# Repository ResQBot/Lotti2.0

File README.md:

# Lotti2.0 by Res.Q Bots Austria

Lotti2.0 is the seccond generation of our tracked **U**rban **S**earch and **E**xploration **R**obot (or USER).

We hope that any info you find in this repository helps you in your quest to develop your own USER, or robot of any other kind.
If you have any questions or want to partner up, feel free to contact us.

## Repository content:

### getting_started
contains a (more or less) detailed introduction to the whole topic of using Ubuntu and ROS, using our ROS packages and how to develop your own. This is a work in progress and you will definitely need addittional information to get deeper into ROS development.

### hardware
contains all (more or less) the hardware information and the CAD files.

### resources
contains user manuals, guidebooks, datasheets, etc. for motory, sensors, parts, ... used in our current robot.

### src 
contains our **ROS2 code** to control the robot and make use of its sensors.

### external

[#external](#external)

Enthält externe Abhängigkeiten, die als Git-Submodule eingebunden sind:

- **[athena](https://github.com/tu-darmstadt-ros-pkg/athena)** (TU Darmstadt) – wir nutzen daraus
  das ESP32-basierte E-Stop-System (`E-Stop`-Ordner im Submodule) für die Not-Aus-Funktionalität.
- **[hector_ros2_utils](https://github.com/tu-darmstadt-ros-pkg/hector_ros2_utils)** (TU Darmstadt) –
  Basis-Utility-Bibliothek, die von der E-Stop-ROS2-Node benötigt wird.

Beide Repos stehen unter MIT-Lizenz. Vielen Dank an das TU-Darmstadt-Team für die Bereitstellung!

#### Setup

Da dieses Repo Submodule enthält, beim Klonen unbedingt `--recurse-submodules` verwenden:

\`\`\`bash
git clone --recurse-submodules https://github.com/ResQBot/Lotti2.0.git
\`\`\`

Falls bereits ohne diese Option geklont wurde, nachträglich:

\`\`\`bash
git submodule update --init --recursive
\`\`\`
&nbsp;
## Disclaimer
Please remember, that we are not professionals in the field of robotics, but merely curious students fooling around. While (most) code and designs you'll find here may work for us, they might not work for you and we do not take any responsibility for potential danger arising from the use of our ideas.

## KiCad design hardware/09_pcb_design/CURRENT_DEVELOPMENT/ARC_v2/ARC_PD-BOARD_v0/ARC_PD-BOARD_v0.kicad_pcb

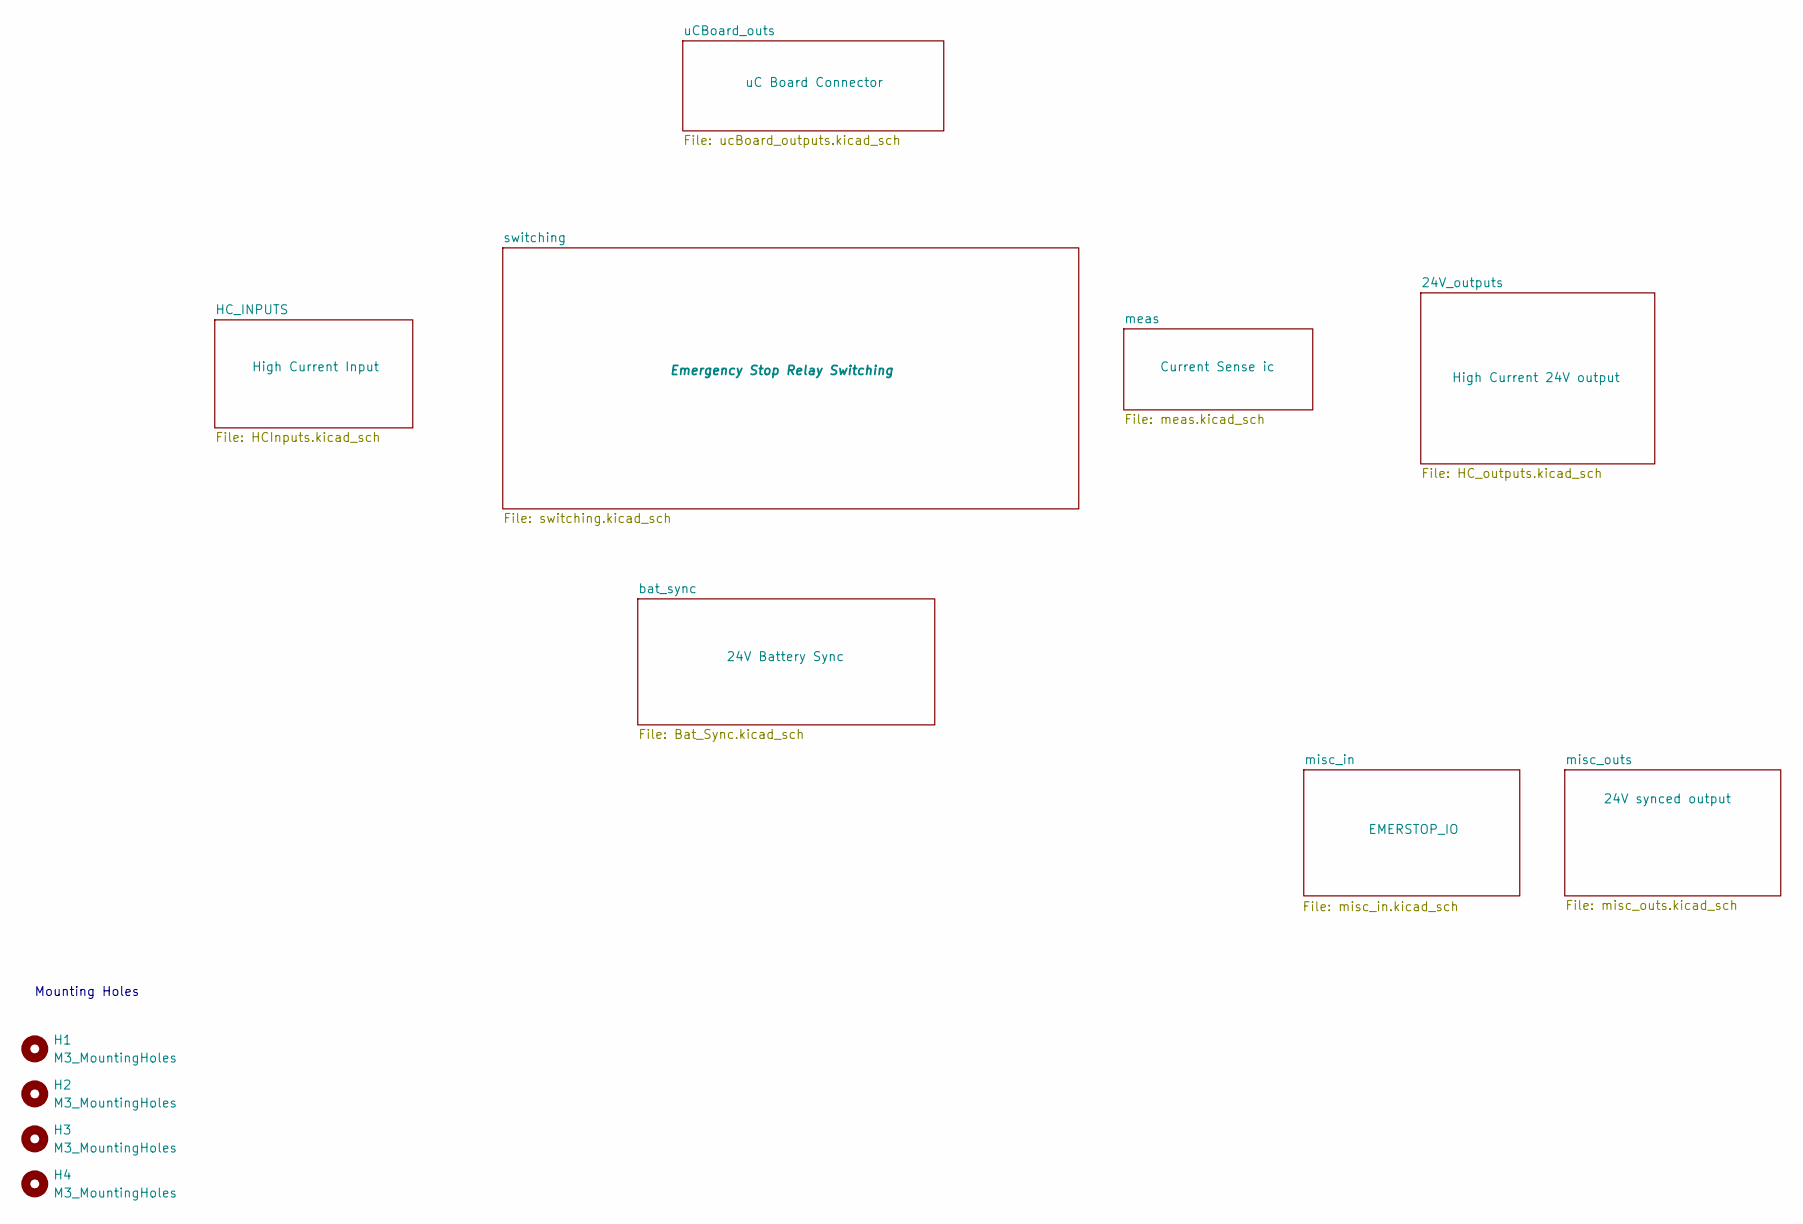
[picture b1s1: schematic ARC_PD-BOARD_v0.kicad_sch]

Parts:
H1, H2, H3, H4: M3_MountingHoles; MountingHole_3.2mm_M3

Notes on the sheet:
Mounting Holes

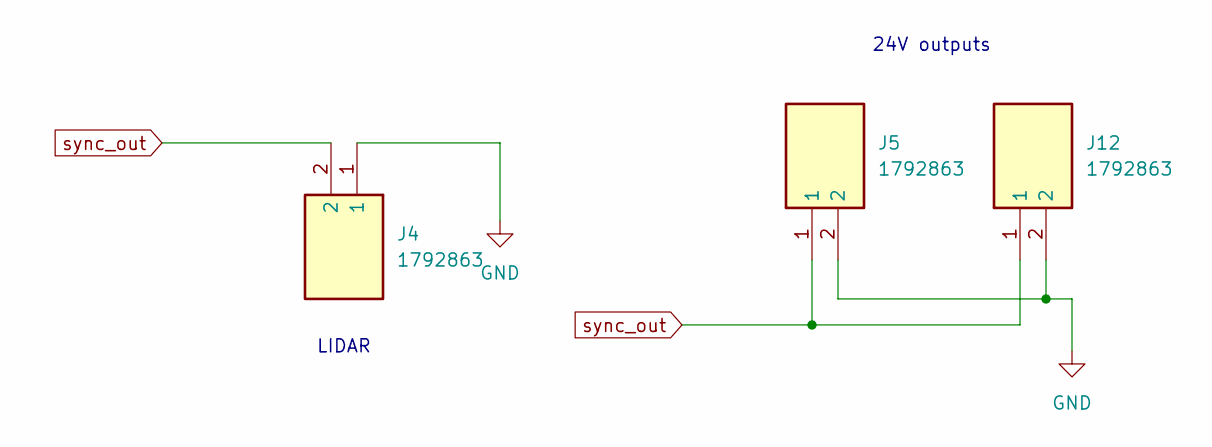
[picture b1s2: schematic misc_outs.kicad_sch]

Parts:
J4, J5, J12: 1792863; Mouser Part Number 651-1792863

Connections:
GND: J4.1, J5.2, J12.2; also elsewhere on the board
sync_out: J4.2, J5.1, J12.1; also elsewhere on the board

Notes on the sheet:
LIDAR
24V outputs

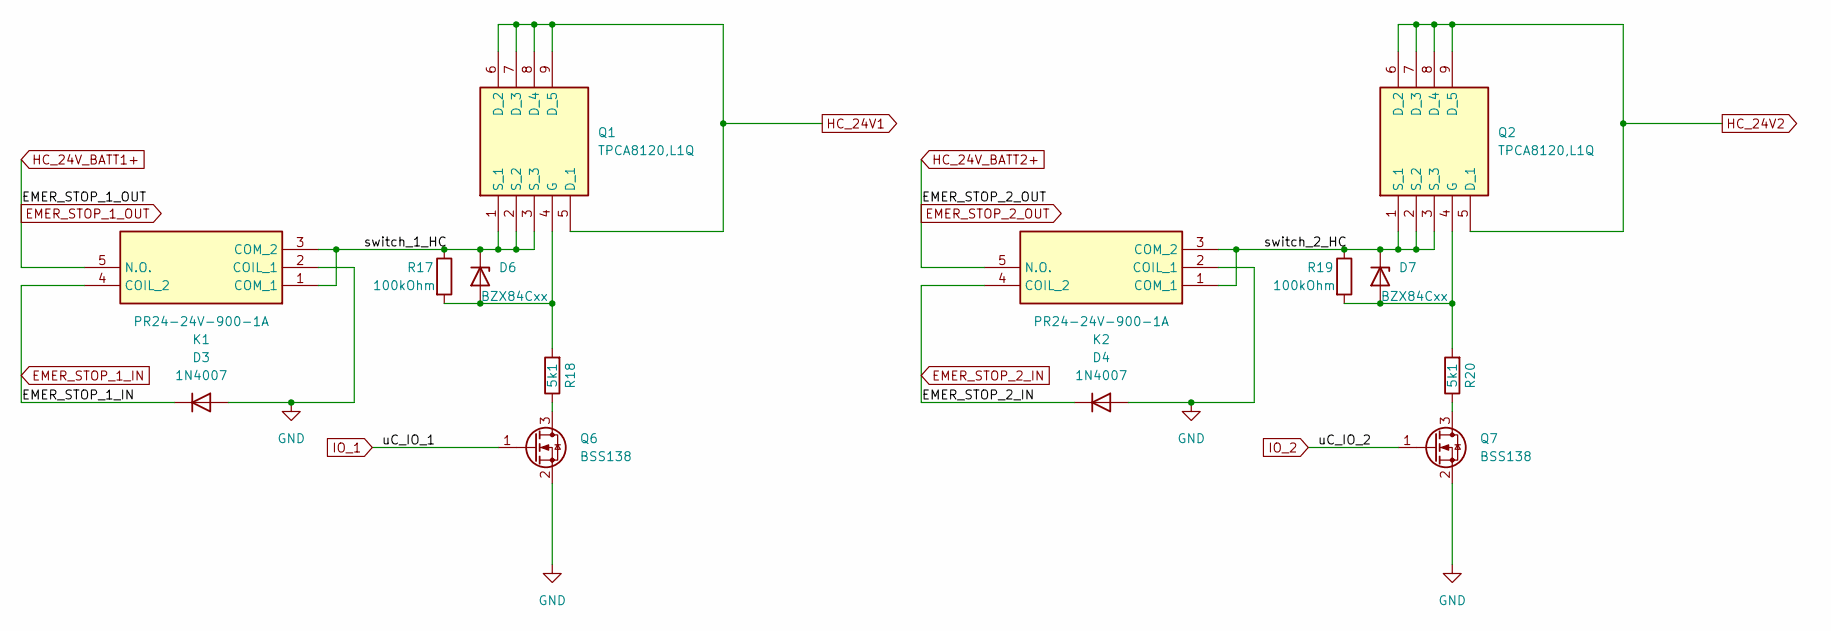
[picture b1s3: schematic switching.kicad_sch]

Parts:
D3, D4: 1N4007; D_DO-41_SOD81_P10.16mm_Horizontal
D6, D7: BZX84Cxx; SOT-23
K1, K2: PR24-24V-900-1A; PR2424V9001A; Mouser Part Number 179-PR24-24V-900-1A
Q1, Q2: TPCA8120,L1Q; TPH4R003NLL1Q; Mouser Part Number 757-TPCA8120L1Q
Q6, Q7: BSS138; SOT-23
R17, R19: 100kOhm; R_1206_3216Metric_Pad1.30x1.75mm_HandSolder
R18, R20: 5k1; R_1206_3216Metric_Pad1.30x1.75mm_HandSolder

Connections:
/switching/switch_1_HC: D6.3 (K), K1.1 (COM_1), K1.3 (COM_2), Q1.1 (S_1), Q1.2 (S_2), Q1.3 (S_3), R17.1
/switching/switch_2_HC: D7.3 (K), K2.1 (COM_1), K2.3 (COM_2), Q2.1 (S_1), Q2.2 (S_2), Q2.3 (S_3), R19.1
EMER_STOP_1_IN: D3.1 (K), K1.4 (COIL_2); also elsewhere on the board
EMER_STOP_1_OUT: K1.5 (N.O.); also elsewhere on the board
EMER_STOP_2_IN: D4.1 (K), K2.4 (COIL_2); also elsewhere on the board
EMER_STOP_2_OUT: K2.5 (N.O.); also elsewhere on the board
GND: D3.2 (A), D4.2 (A), K1.2 (COIL_1), K2.2 (COIL_1), Q6.2 (S), Q7.2 (S); also elsewhere on the board
HC_24V1: Q1.5 (D_1), Q1.6 (D_2), Q1.7 (D_3), Q1.8 (D_4), Q1.9 (D_5); also elsewhere on the board
HC_24V2: Q2.5 (D_1), Q2.6 (D_2), Q2.7 (D_3), Q2.8 (D_4), Q2.9 (D_5); also elsewhere on the board
IO_1: Q6.1 (G); also elsewhere on the board
IO_2: Q7.1 (G); also elsewhere on the board
unnamed: D6.1 (A), Q1.4 (G), R17.2, R18.2
unnamed: D7.1 (A), Q2.4 (G), R19.2, R20.2
unnamed: Q6.3 (D), R18.1
unnamed: Q7.3 (D), R20.1

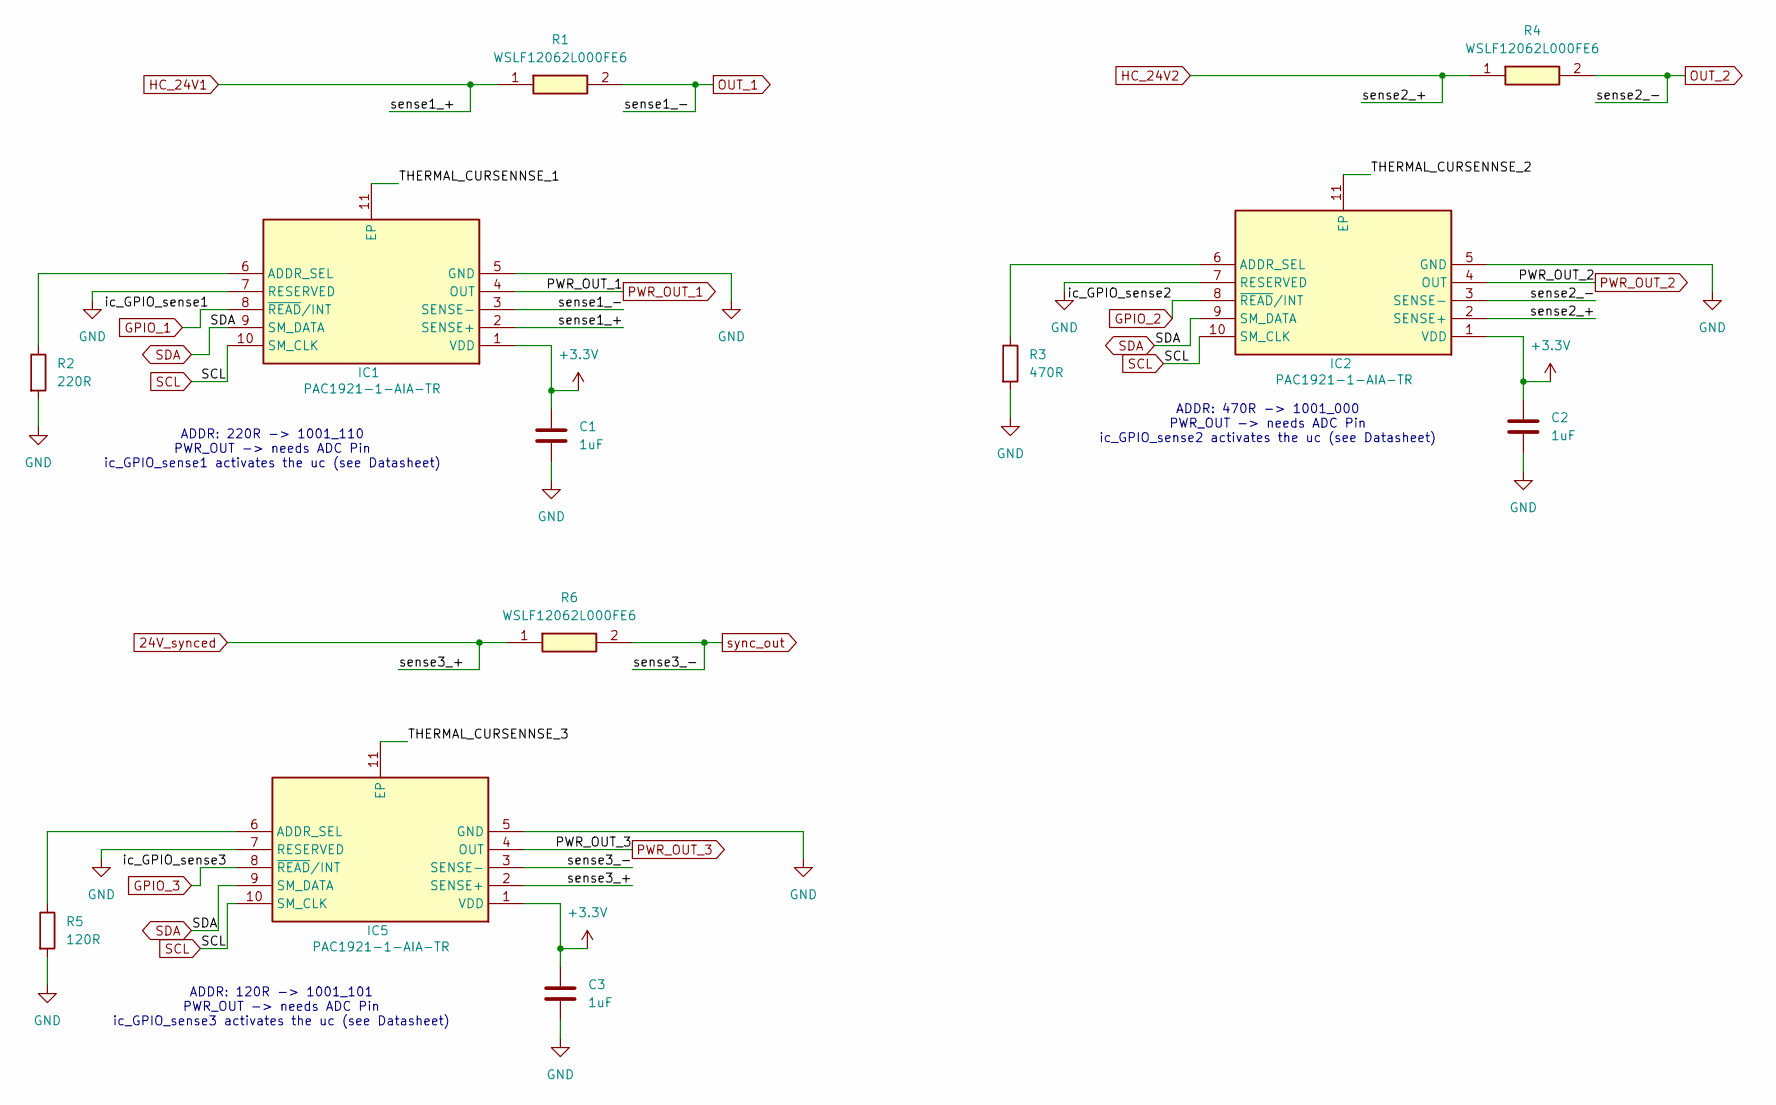
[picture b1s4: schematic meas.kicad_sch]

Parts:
C1, C2, C3: 1uF; C_1206_3216Metric_Pad1.33x1.80mm_HandSolder
IC1, IC2, IC5: PAC1921-1-AIA-TR; SON50P300X300X90-11N-D; Mouser Part Number 579-PAC1921-1-AIA-TR
R1, R4, R6: WSLF12062L000FE6; R_1206_3216Metric_Pad1.30x1.75mm_HandSolder; Manufacturer_Part_Number WSLF12062L000FE6
R2: 220R; R_0805_2012Metric_Pad1.20x1.40mm_HandSolder
R3: 470R; R_0805_2012Metric_Pad1.20x1.40mm_HandSolder
R5: 120R; R_0805_2012Metric_Pad1.20x1.40mm_HandSolder

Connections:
24V_synced: IC5.2 (SENSE+), R6.1; also elsewhere on the board
+3.3V: C1.1, C2.1, C3.1, IC1.1 (VDD), IC2.1 (VDD), IC5.1 (VDD); also elsewhere on the board
/meas/THERMAL_CURSENNSE_1: IC1.11 (EP)
/meas/THERMAL_CURSENNSE_2: IC2.11 (EP)
/meas/THERMAL_CURSENNSE_3: IC5.11 (EP)
GND: C1.2, C2.2, C3.2, IC1.5 (GND), IC1.7 (RESERVED), IC2.5 (GND), IC2.7 (RESERVED), IC5.5 (GND), IC5.7 (RESERVED), R2.2, R3.2, R5.2; also elsewhere on the board
GPIO_1: IC1.8 (~READ/INT); also elsewhere on the board
GPIO_2: IC2.8 (~READ/INT); also elsewhere on the board
GPIO_3: IC5.8 (~READ/INT); also elsewhere on the board
HC_24V1: IC1.2 (SENSE+), R1.1; also elsewhere on the board
HC_24V2: IC2.2 (SENSE+), R4.1; also elsewhere on the board
unnamed: IC1.6 (ADDR_SEL), R2.1
unnamed: IC2.6 (ADDR_SEL), R3.1
unnamed: IC5.6 (ADDR_SEL), R5.1
OUT_1: IC1.3 (SENSE-), R1.2; also elsewhere on the board
OUT_2: IC2.3 (SENSE-), R4.2; also elsewhere on the board
PWR_OUT_1: IC1.4 (OUT); also elsewhere on the board
PWR_OUT_2: IC2.4 (OUT); also elsewhere on the board
PWR_OUT_3: IC5.4 (OUT); also elsewhere on the board
SCL: IC1.10 (SM_CLK), IC2.10 (SM_CLK), IC5.10 (SM_CLK); also elsewhere on the board
SDA: IC1.9 (SM_DATA), IC2.9 (SM_DATA), IC5.9 (SM_DATA); also elsewhere on the board
sync_out: IC5.3 (SENSE-), R6.2; also elsewhere on the board

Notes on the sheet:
ADDR: 120R -> 1001_101 PWR_OUT -> needs ADC Pin ic_GPIO_sense3 activates the uc (see Datasheet)
ADDR: 220R -> 1001_110 PWR_OUT -> needs ADC Pin ic_GPIO_sense1 activates the uc (see Datasheet)
ADDR: 470R -> 1001_000 PWR_OUT -> needs ADC Pin ic_GPIO_sense2 activates the uc (see Datasheet)

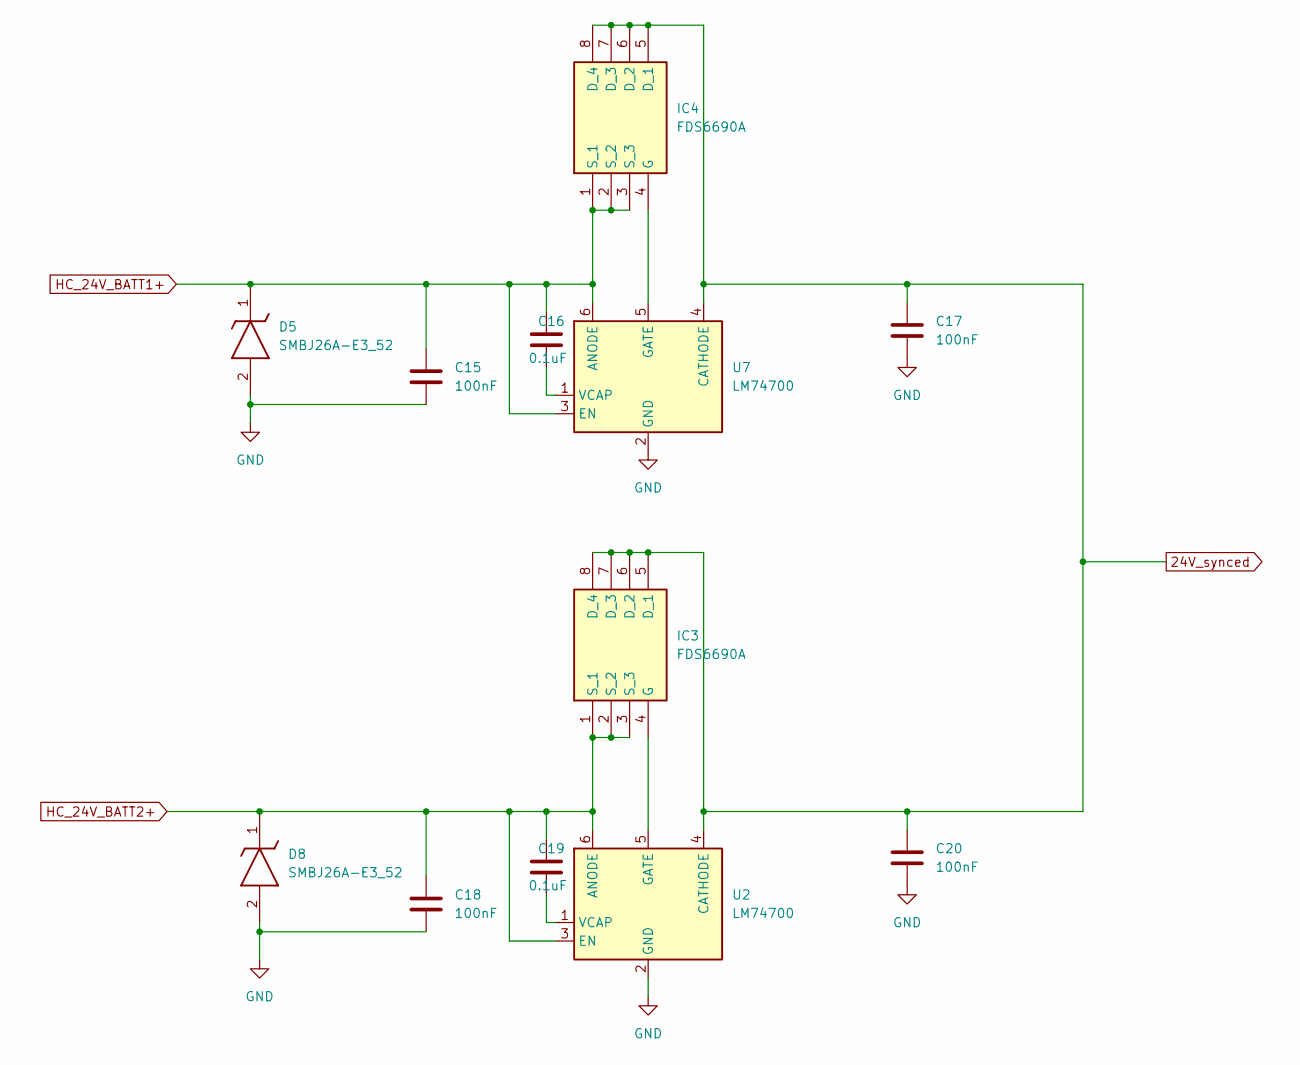
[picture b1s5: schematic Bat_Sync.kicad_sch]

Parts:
C15, C17, C18, C20: 100nF; C_0805_2012Metric_Pad1.18x1.45mm_HandSolder
C16, C19: 0.1uF; C_0805_2012Metric_Pad1.18x1.45mm_HandSolder
D5, D8: SMBJ26A-E3_52; DIOM5436X244N; Mouser Part Number 625-SMBJ26A-E3
IC3, IC4: FDS6690A; SOIC127P600X175-8N; Mouser Part Number 512-FDS6690A
U2, U7: LM74700; SOT-23-6

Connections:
24V_synced: C17.1, C20.1, IC3.5 (D_1), IC3.6 (D_2), IC3.7 (D_3), IC3.8 (D_4), IC4.5 (D_1), IC4.6 (D_2), IC4.7 (D_3), IC4.8 (D_4), U2.4 (CATHODE), U7.4 (CATHODE); also elsewhere on the board
EMER_STOP_1_OUT: C15.1, C16.1, D5.1 (K), IC4.1 (S_1), IC4.2 (S_2), IC4.3 (S_3), U7.3 (EN), U7.6 (ANODE); also elsewhere on the board
EMER_STOP_2_OUT: C18.1, C19.1, D8.1 (K), IC3.1 (S_1), IC3.2 (S_2), IC3.3 (S_3), U2.3 (EN), U2.6 (ANODE); also elsewhere on the board
GND: C15.2, C17.2, C18.2, C20.2, D5.2 (A), D8.2 (A), U2.2 (GND), U7.2 (GND); also elsewhere on the board
unnamed: IC3.4 (G), U2.5 (GATE)
unnamed: IC4.4 (G), U7.5 (GATE)
unnamed: C19.2, U2.1 (VCAP)
unnamed: C16.2, U7.1 (VCAP)

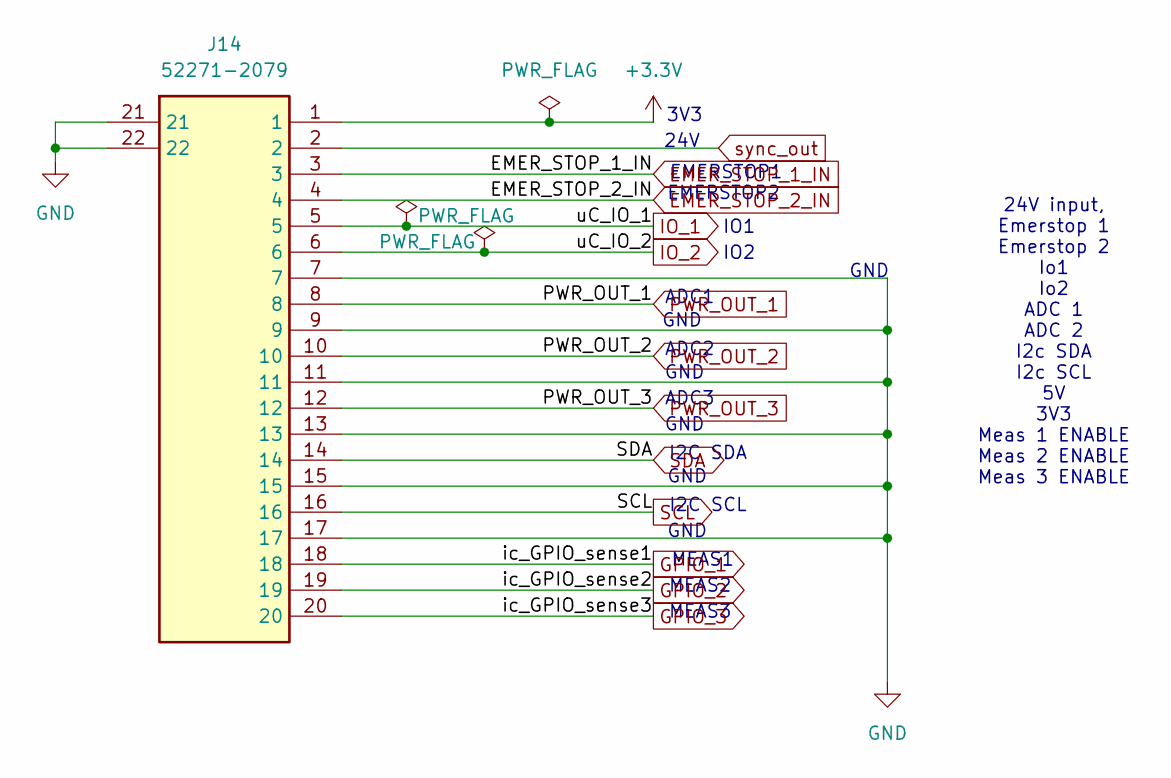
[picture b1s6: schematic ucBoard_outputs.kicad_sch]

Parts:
J14: 52271-2079; 522712079; Mouser Part Number 538-52271-2079

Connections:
+3.3V: J14.1; also elsewhere on the board
EMER_STOP_1_IN: J14.3; also elsewhere on the board
EMER_STOP_2_IN: J14.4; also elsewhere on the board
GND: J14.7, J14.9, J14.11, J14.13, J14.15, J14.17, J14.21, J14.22; also elsewhere on the board
GPIO_1: J14.18; also elsewhere on the board
GPIO_2: J14.19; also elsewhere on the board
GPIO_3: J14.20; also elsewhere on the board
IO_1: J14.5; also elsewhere on the board
IO_2: J14.6; also elsewhere on the board
PWR_OUT_1: J14.8; also elsewhere on the board
PWR_OUT_2: J14.10; also elsewhere on the board
PWR_OUT_3: J14.12; also elsewhere on the board
SCL: J14.16; also elsewhere on the board
SDA: J14.14; also elsewhere on the board
sync_out: J14.2; also elsewhere on the board

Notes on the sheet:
GND
EMERSTOP1
ADC3
I2C SCL
IO2
GND
MEAS1
3V3
MEAS3
I2C SDA
MEAS2
24V input, Emerstop 1 Emerstop 2 Io1 Io2 ADC 1 ADC 2 I2c SDA I2c SCL 5V 3V3 Meas 1 ENABLE Meas 2 ENABLE Meas 3 ENABLE
24V
ADC2
EMERSTOP2
ADC1
IO1

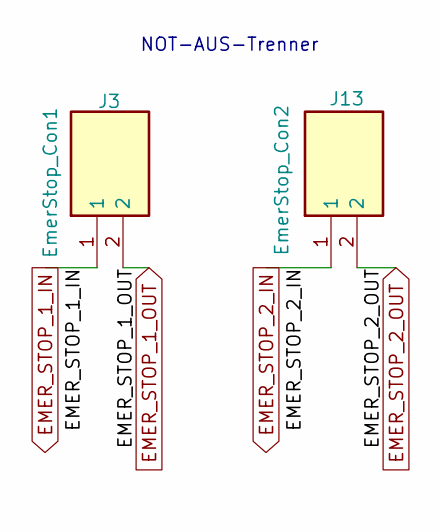
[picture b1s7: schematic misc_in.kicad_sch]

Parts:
J3: EmerStop_Con1; 25SHB02TR; PARTREV N/A
J13: EmerStop_Con2; 25SHB02TR; PARTREV N/A

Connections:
EMER_STOP_1_IN: J3.1; also elsewhere on the board
EMER_STOP_1_OUT: J3.2; also elsewhere on the board
EMER_STOP_2_IN: J13.1; also elsewhere on the board
EMER_STOP_2_OUT: J13.2; also elsewhere on the board

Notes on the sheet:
NOT-AUS-Trenner

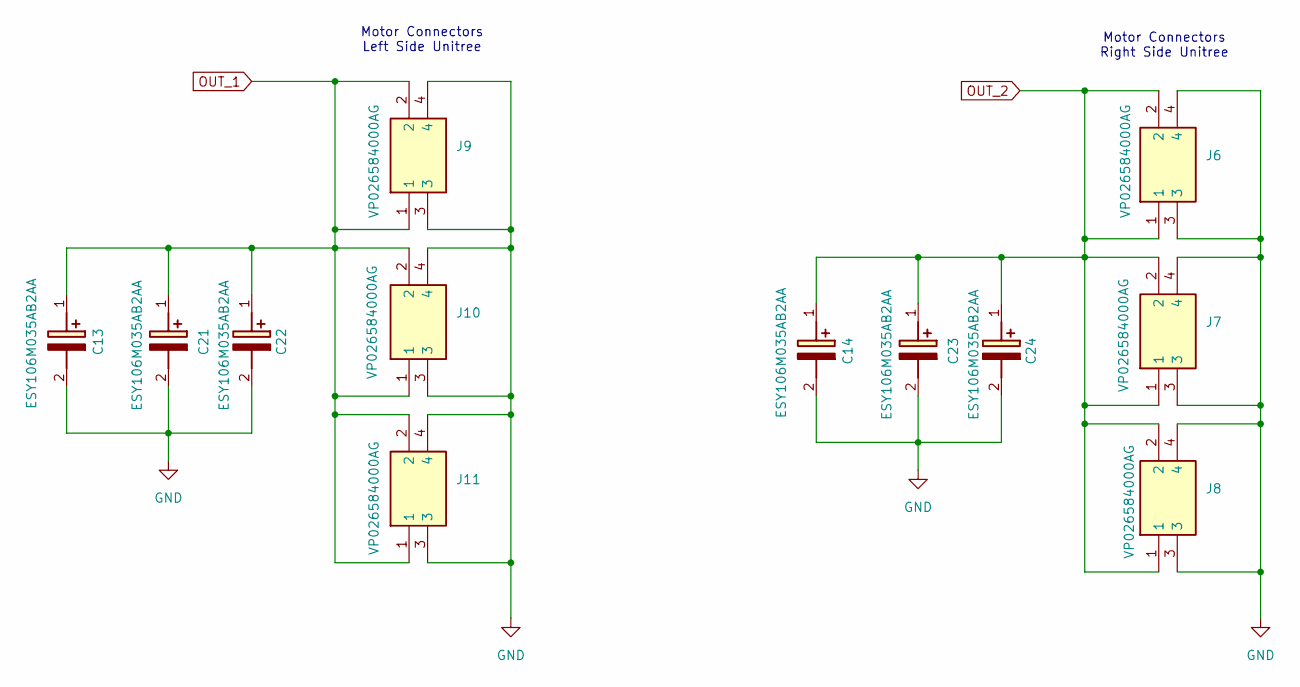
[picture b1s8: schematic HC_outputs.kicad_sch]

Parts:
C13, C14, C21, C22, C23, C24: ESY106M035AB2AA; CAPPRD150W45D400H850; Mouser Part Number 80-ESY106M035AB2AA
J6, J7, J8, J9, J10, J11: VP026584000AG; SHDR4W100P1016_2X2_2032X1830X2850P; Manufacturer_Part_Number VP026584000AG; Mouser Part Number 523-VP026584000AG

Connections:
GND: C13.2 (-), C14.2 (-), C21.2 (-), C22.2 (-), C23.2 (-), C24.2 (-), J6.3, J6.4, J7.3, J7.4, J8.3, J8.4, J9.3, J9.4, J10.3, J10.4, J11.3, J11.4; also elsewhere on the board
OUT_1: C13.1 (+), C21.1 (+), C22.1 (+), J9.1, J9.2, J10.1, J10.2, J11.1, J11.2; also elsewhere on the board
OUT_2: C14.1 (+), C23.1 (+), C24.1 (+), J6.1, J6.2, J7.1, J7.2, J8.1, J8.2; also elsewhere on the board

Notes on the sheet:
Motor Connectors Left Side Unitree
Motor Connectors Right Side Unitree

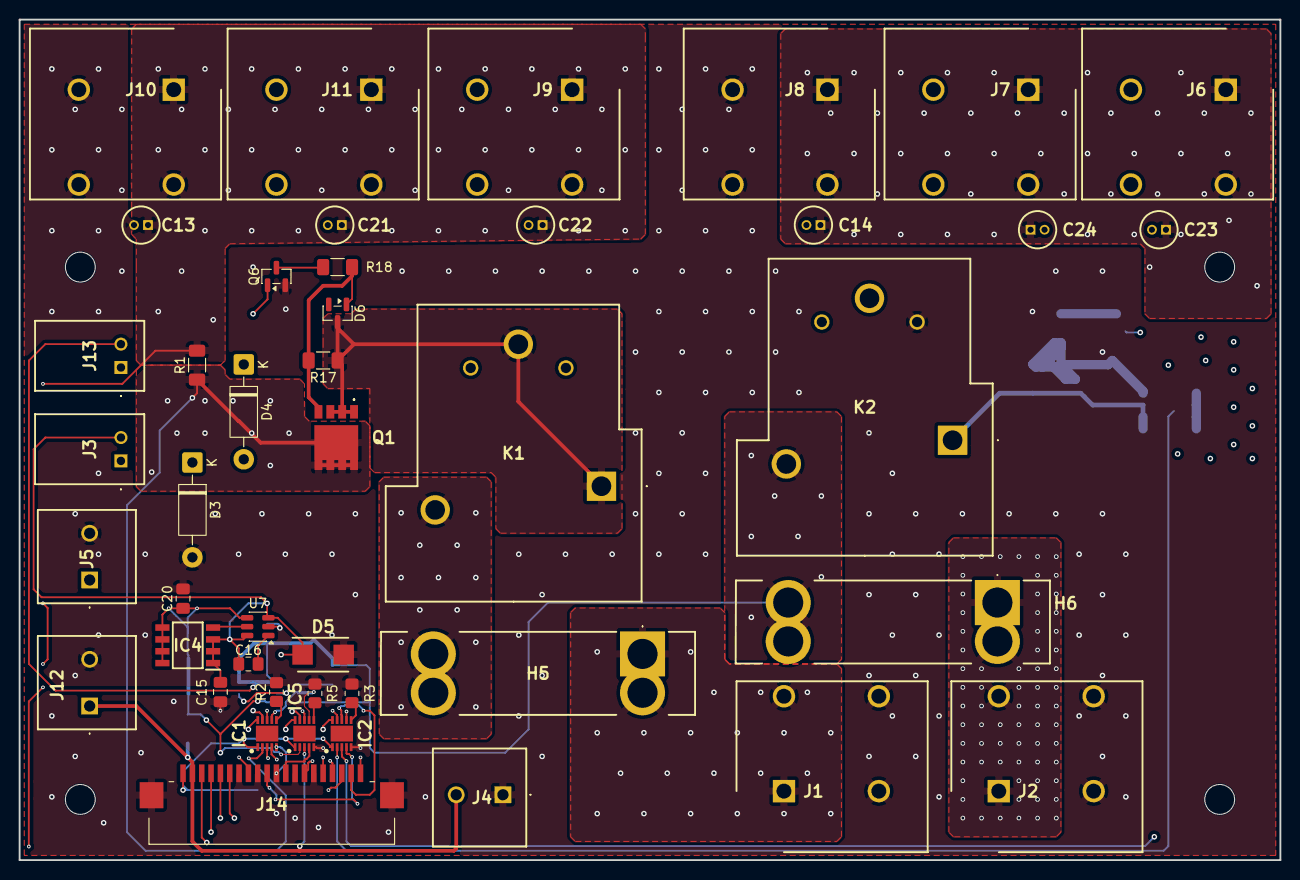
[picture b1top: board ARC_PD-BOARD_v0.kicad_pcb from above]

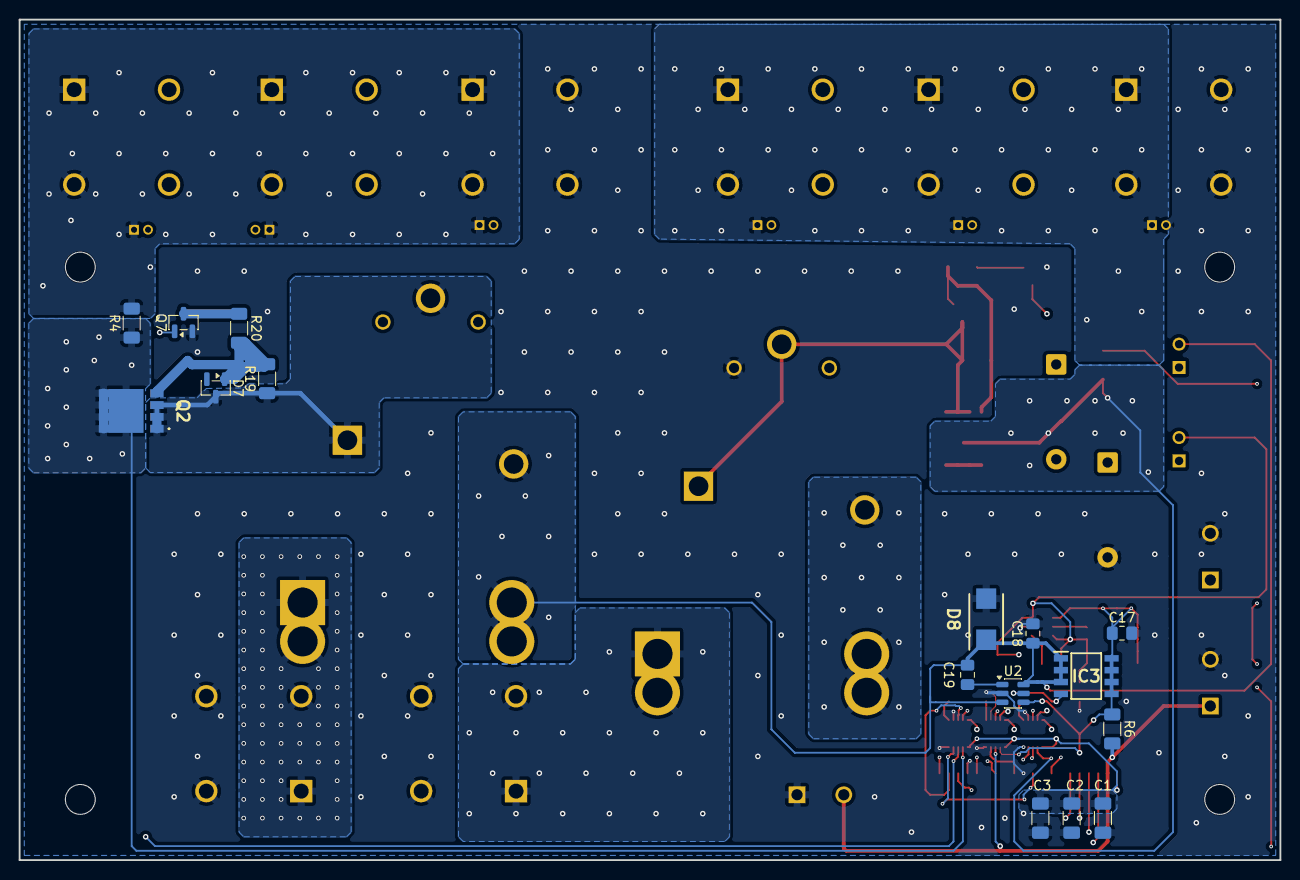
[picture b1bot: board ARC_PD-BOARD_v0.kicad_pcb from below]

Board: 4 copper layers, 135.0 x 90.0 mm, 64 parts (16 on the bottom side), 37 nets.

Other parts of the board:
H5, H6: 3581
J1, J2: VP026584000AG; SHDR4W100P1016_2X2_2032X1830X2850P

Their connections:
/HC_INPUTS/HC_24V_BATT1_INPUT: H5.1, H5.2, J1.1, J1.2
/HC_INPUTS/HC_24V_BATT2_INPUT: H6.1, H6.2, J2.1, J2.2
EMER_STOP_1_OUT: H5.3, H5.4; also elsewhere on the board
EMER_STOP_2_OUT: H6.3, H6.4; also elsewhere on the board
GND: J1.3, J1.4, J2.3, J2.4; also elsewhere on the board
